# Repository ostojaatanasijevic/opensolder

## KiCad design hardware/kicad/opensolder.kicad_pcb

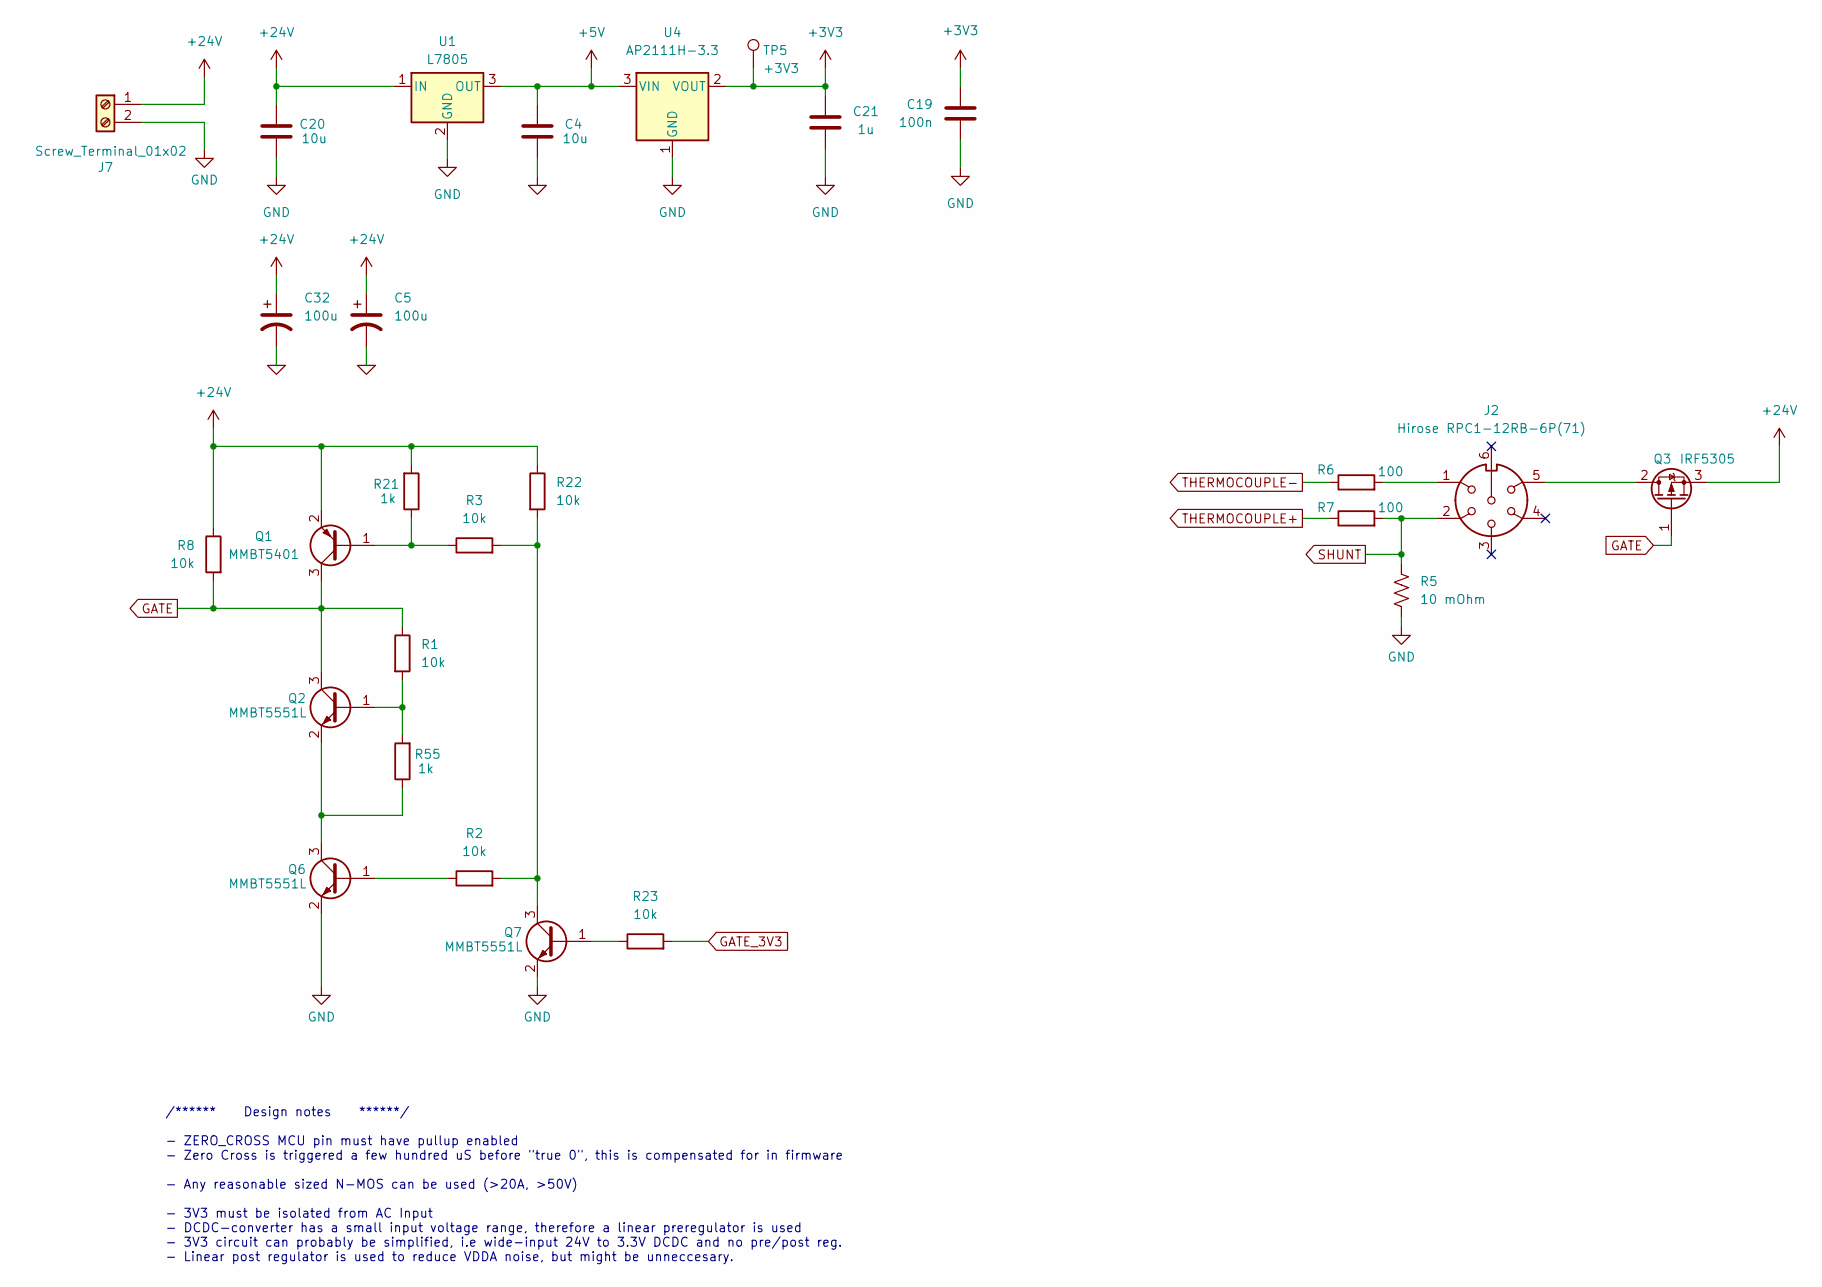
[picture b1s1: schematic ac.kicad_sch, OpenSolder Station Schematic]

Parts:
C4, C20: 10u; C_0603_1608Metric_Pad1.08x0.95mm_HandSolder; LCSC C96446
C5, C32: 100u; CP_Radial_D8.0mm_P3.50mm; Part number UCY2V220MPD9TD
C19: 100n; C_0603_1608Metric_Pad1.08x0.95mm_HandSolder; LCSC C14663
C21: 1u; C_0603_1608Metric_Pad1.08x0.95mm_HandSolder; LCSC C15849
J2: Hirose RPC1-12RB-6P(71); Hirose_RPC1
J7: Screw_Terminal_01x02; TerminalBlock_Phoenix_MKDS-1,5-2-5.08_1x02_P5.08mm_Horizont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
Q1: MMBT5401; SOT-23; LCSC C8326
Q2, Q6, Q7: MMBT5551L; SOT-23; LCSC C2145
Q3: IRF5305; TO-220-3_Vertical
R1, R2, R3, R8, R22, R23: 10k; R_0603_1608Metric_Pad0.98x0.95mm_HandSolder; LCSC C25804
R5: 10 mOhm; R_2512_6332Metric_Pad1.40x3.35mm_HandSolder
R6, R7: 100; R_0603_1608Metric_Pad0.98x0.95mm_HandSolder; LCSC C22775
R21, R55: 1k; R_0603_1608Metric_Pad0.98x0.95mm_HandSolder; LCSC C21190
TP5: +3V3; TestPoint_Pad_D1.0mm
U1: L7805; TO-220-3_Vertical
U4: AP2111H-3.3; SOT-223

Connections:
0: C5.2, C32.2
+3V3: C19.2, C21.1, TP5.1, U4.2 (VOUT); also elsewhere on the board
+5V: C4.1, U1.3 (OUT), U4.3 (VIN); also elsewhere on the board
+24V: C5.1, C20.1, C32.1, J7.1, Q1.2 (E), Q3.3 (S), R8.1, R21.2, R22.1, U1.1 (IN)
GATE: Q1.3 (C), Q2.3 (C), Q3.1 (G), R1.1, R8.2
GATE_3V3: R23.2
GND: C4.2, C19.1, C20.2, C21.2, J7.2, Q6.2 (E), Q7.2 (E), R5.2, U1.2 (GND), U4.1 (GND); also elsewhere on the board
unnamed: J2.1, R6.2
unnamed: Q1.1 (B), R3.1, R21.1
unnamed: Q2.1 (B), R1.2, R55.2
unnamed: Q2.2 (E), Q6.3 (C), R55.1
unnamed: J2.5, Q3.2 (D)
unnamed: Q6.1 (B), R2.1
unnamed: Q7.1 (B), R23.1
unnamed: Q7.3 (C), R2.2, R3.2, R22.2
SHUNT: J2.2, R5.1, R7.2; also elsewhere on the board
THERMOCOUPLE+: R7.1; also elsewhere on the board
THERMOCOUPLE-: R6.1; also elsewhere on the board

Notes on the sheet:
/****** Design notes ******/ - ZERO_CROSS MCU pin must have pullup enabled - Zero Cross is triggered a few hundred uS before "true 0", this is compensated for in firmware - Any reasonable sized N-MOS can be used (>20A, >50V) - 3V3 must be isolated from AC Input - DCDC-converter has a small input vo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

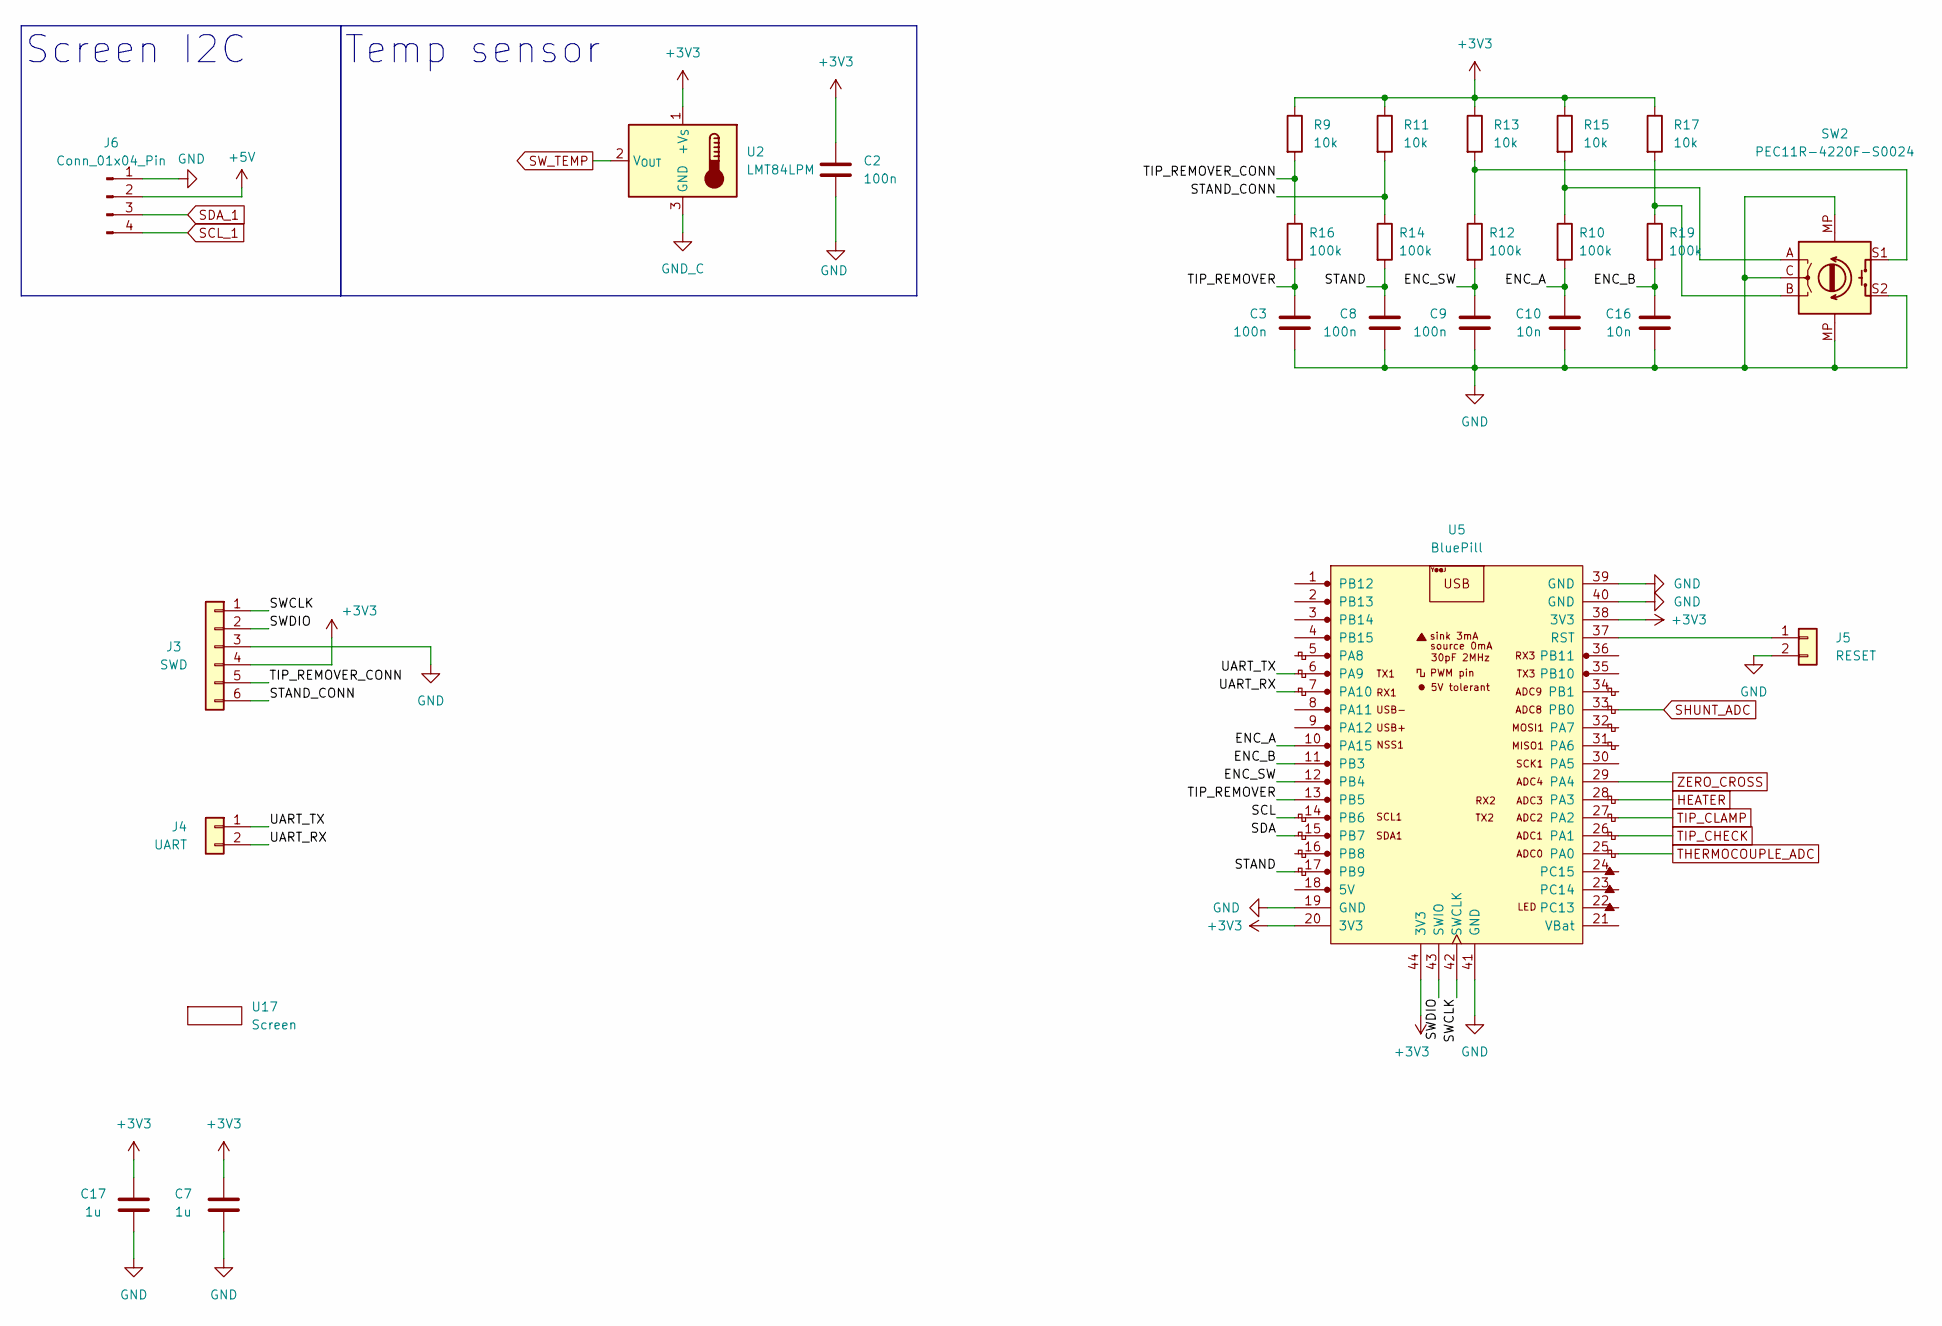
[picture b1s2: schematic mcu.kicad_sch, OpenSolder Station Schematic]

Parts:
C2, C3, C8, C9: 100n; C_0603_1608Metric_Pad1.08x0.95mm_HandSolder; LCSC C14663
C7, C17: 1u; C_0603_1608Metric_Pad1.08x0.95mm_HandSolder; LCSC C15849
C10, C16: 10n; C_0603_1608Metric_Pad1.08x0.95mm_HandSolder; LCSC C57112
J3: SWD; IDC-Header_2x03_P2.54mm_Vertical
J4: UART; PinSocket_1x02_P2.54mm_Vertical
J5: RESET; PinSocket_1x02_P2.54mm_Vertical
J6: Conn_01x04_Pin; PinHeader_1x04_P2.54mm_Vertical
R9, R11, R13, R15, R17: 10k; R_0603_1608Metric_Pad0.98x0.95mm_HandSolder; LCSC C25804
R10, R12, R14, R16, R19: 100k; R_0603_1608Metric_Pad0.98x0.95mm_HandSolder; LCSC C25803
SW2: PEC11R-4220F-S0024; RotaryEncoder_PEC11R_PEC12R
U2: LMT84LPM; TO-92_Inline_W4.0mm_Horizontal_FlatSideDown
U5: BluePill
U17: Screen; WC1602A

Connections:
+3V3: C2.2, C7.1, C17.1, J3.4, R9.1, R11.1, R13.1, R15.1, R17.1, U2.1 (+V_{S}), U5.20 (3V3), U5.38 (3V3), U5.44 (3V3); also elsewhere on the board
+5V: J6.2; also elsewhere on the board
/MCU/ENC_A: C10.2, R10.2, U5.10 (PA15)
/MCU/ENC_B: C16.2, R19.2, U5.11 (PB3)
/MCU/ENC_SW: C9.2, R12.2, U5.12 (PB4)
/MCU/SCL: U5.14 (PB6)
/MCU/SDA: U5.15 (PB7)
/MCU/STAND: C8.2, R14.2, U5.17 (PB9)
/MCU/STAND_CONN: J3.6, R11.2, R14.1
/MCU/SWCLK: J3.1, U5.42 (SWCLK)
/MCU/SWDIO: J3.2, U5.43 (SWIO)
/MCU/TIP_REMOVER: C3.2, R16.2, U5.13 (PB5)
/MCU/TIP_REMOVER_CONN: J3.5, R9.2, R16.1
/MCU/UART_RX: J4.2, U5.7 (PA10)
/MCU/UART_TX: J4.1, U5.6 (PA9)
GND: C2.1, C3.1, C7.2, C8.1, C9.1, C10.1, C16.1, C17.2, J3.3, J5.2, J6.1, SW2.C, SW2.MP, SW2.S2, U5.19 (GND), U5.39 (GND), U5.40 (GND), U5.41 (GND); also elsewhere on the board
GND_C: U2.3 (GND)
HEATER: U5.28 (PA3)
unnamed: J5.1, U5.37 (RST)
unnamed: R10.1, R15.2, SW2.A
unnamed: R12.1, R13.2, SW2.S1
unnamed: R17.2, R19.1, SW2.B
SCL_1: J6.4
SDA_1: J6.3
SHUNT_ADC: U5.33 (PB0); also elsewhere on the board
SW_TEMP: U2.2 (V_{OUT})
THERMOCOUPLE_ADC: U5.25 (PA0); also elsewhere on the board
TIP_CHECK: U5.26 (PA1)
TIP_CLAMP: U5.27 (PA2)
ZERO_CROSS: U5.29 (PA4)

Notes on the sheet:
Screen I2C
Temp sensor

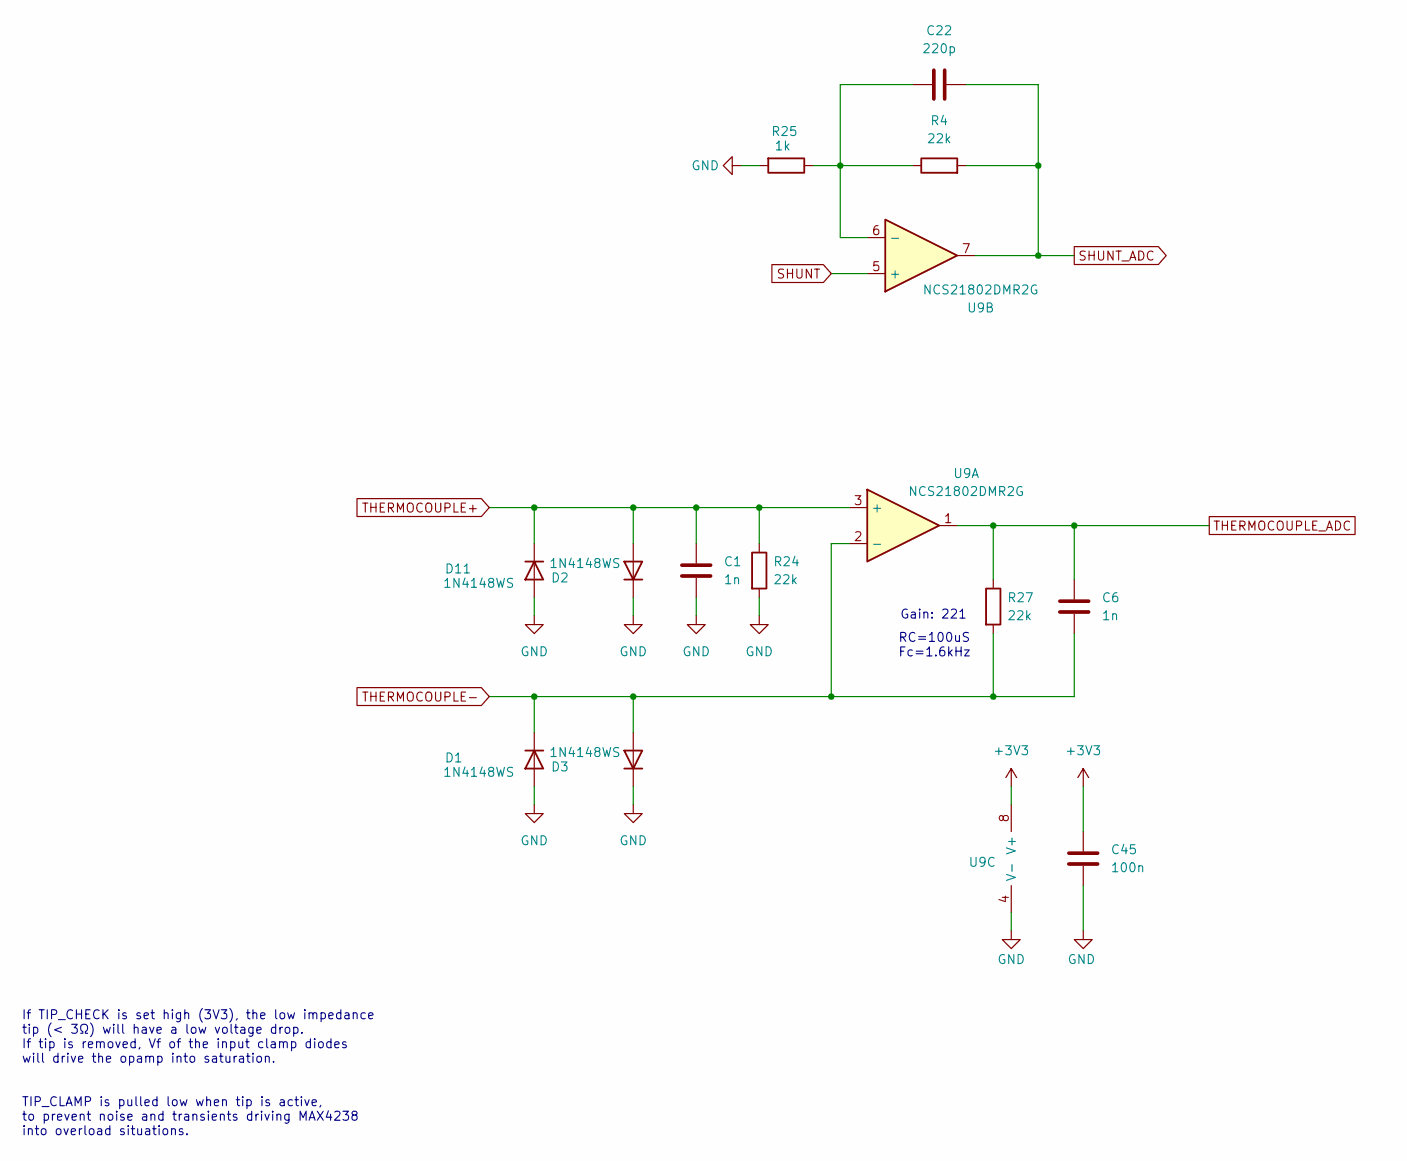
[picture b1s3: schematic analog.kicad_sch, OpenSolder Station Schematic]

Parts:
C1, C6: 1n; C_0603_1608Metric_Pad1.08x0.95mm_HandSolder; LCSC C1588
C22: 220p; C_0603_1608Metric_Pad1.08x0.95mm_HandSolder; LCSC C1603
C45: 100n; C_0603_1608Metric_Pad1.08x0.95mm_HandSolder; LCSC C14663
D1, D2, D3, D11: 1N4148WS; D_SOD-323; LCSC C2128
R4, R24, R27: 22k; R_0603_1608Metric_Pad0.98x0.95mm_HandSolder; LCSC C31850
R25: 1k; R_0603_1608Metric_Pad0.98x0.95mm_HandSolder; LCSC C21190
U9: NCS21802DMR2G; OnSemi_Micro8

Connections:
+3V3: C45.2, U9.8 (V+); also elsewhere on the board
GND: C1.1, C45.1, D1.2 (A), D2.1 (K), D3.1 (K), D11.2 (A), R24.2, R25.2, U9.4 (V-); also elsewhere on the board
unnamed: C22.1, R4.1, R25.1, U9.6 (-)
SHUNT: U9.5 (+); also elsewhere on the board
SHUNT_ADC: C22.2, R4.2, U9.7; also elsewhere on the board
THERMOCOUPLE+: C1.2, D2.2 (A), D11.1 (K), R24.1, U9.3 (+); also elsewhere on the board
THERMOCOUPLE-: C6.1, D1.1 (K), D3.2 (A), R27.2, U9.2 (-); also elsewhere on the board
THERMOCOUPLE_ADC: C6.2, R27.1, U9.1; also elsewhere on the board

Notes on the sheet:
Gain: 221
RC=100uS Fc=1.6kHz
If TIP_CHECK is set high (3V3), the low impedance tip (< 3Ω) will have a low voltage drop. If tip is removed, Vf of the input clamp diodes will drive the opamp into saturation. TIP_CLAMP is pulled low when tip is active, to prevent noise and transients driving MAX4238 into overload situations.

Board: 2 copper layers, 66 parts (4 on the bottom side), 35 nets, no tracks yet.

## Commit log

2025-11-02 Schematic update.
2025-11-02 Placement???
2025-12-10 lsdk

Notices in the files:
hardware/kicad/ac.kicad_sch:
Licence: GPL-3.0
